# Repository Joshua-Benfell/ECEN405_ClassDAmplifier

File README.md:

# ECEN405_ClassDAmplifier

# Parts Checklist:
- [ ] [LPF 1](#lpf-1)
- [ ] [LPF 2](#lpf-2)
- [ ] [Gate Drivers](#gate-drivers) x 2
- [ ] Triangle wave generator block 
    - [ x ] [Comparator 1](#comparator-1) 
    - [ ] [Integrator](#integrator)
- [ ] [MOSFETs](#mosfets) x 2
- [ ] [Comparator 2](#comparator) 2
- [ ] [Inverter](#inverter)
- [ ] [Buffer](#buffer)

# System Overview
## Input Voltage
2V Peak to peak (+1V to -1V) with at least 1V input sensitivity. 

## Filters
### **Output Filter**
Needs to filter frequencies above 200Hz, but not the 200Hz point such that it has equivalent gain.  
Will likely need to be a Bridge Tied load (BTL) configuration, as BTL output filters do not require DC blocking caps, which limit the low frequency response of the amplifier, and can be quite large.  

Further reading: [on output filter types for class-d amplifiers](https://www.eetimes.com/understanding-output-filters-for-class-d-amplifiers/) and [BTL configurations on Wikipedia](https://en.wikipedia.org/wiki/Bridged_and_paralleled_amplifiers#Bridge-parallel_amplifier)  

### **Input Filter**
Cut-off point at 2kHz so that the cut-off is 1 decade above the 200Hz at the top of the bandwidth. This will avoid the phase change since it starts 1 decade before the cut-off. Make a Bode plot. No HPF for input as it is not needed. 
## Triangle Wave Generator
Possible approaches:
### **555 timer and an integrator**
To produce a clean triangle wave is complicated with a 555, simpler circuits with a 555 don't seem to guarantee a good output triangle wave. Furthermore, 55 timer circuits are more expensive and have a larger footprint.

### **Comparator integrator** 
A comparator integrator, is able to provide a reliably clean triangle wave and is fairly simple to implement.  
  
The frequency of the triangle wave will be above the audible range of frequencies at 22kHz.  
The package used will be: [MAX4016](https://www.digikey.co.nz/product-detail/en/maxim-integrated/MAX4016ESA/MAX4016ESA-ND/1702288)  
- 10V rail so that we don’t step down more again
- 5V middle because 50/50 v-divider is easy
- No dual rail because that is what a full bridge is for
- Also no whack shit - Danny B

## Switching Frequency
Two key constraints with switching frequency:  
1. As we are sampling an audio signal, it must be at least 10x the max frequency in our signal. The max signal frequency for the amplifier will be 200Hz, therefore the minimum sampling frequency must be 2kHz.
2. The switching frequency can't be audible, which means it must be outside of the audible range of frequencies to humans which is 20Hz - 20kHz. Adult humans typically can't hear more than 15 - 17kHz, making 20kHz a reasonable limit.
As a result the switching frequency must be **at least 20kHz**.

# Part Description and Justification
## LPF 1
## LPF 2
## Gate Drivers
### Requirements
- 18V Input
- 80W at 4 Ohms
- No integrated Fets
- Selectable Dead Time

### Selected
## Comparator 1
[MAX4016](https://www.digikey.co.nz/product-detail/en/maxim-integrated/MAX4016ESA/MAX4016ESA-ND/1702288)  
- 10V rail so that we don’t step down more again
- 5V middle because 50/50 v-divider is easy
- No dual rail because that is what a full bridge is for
- Also no whack shit - Danny B
## Integrator
## MOSFETs
## Comparator 2
## Inverter
## Buffer

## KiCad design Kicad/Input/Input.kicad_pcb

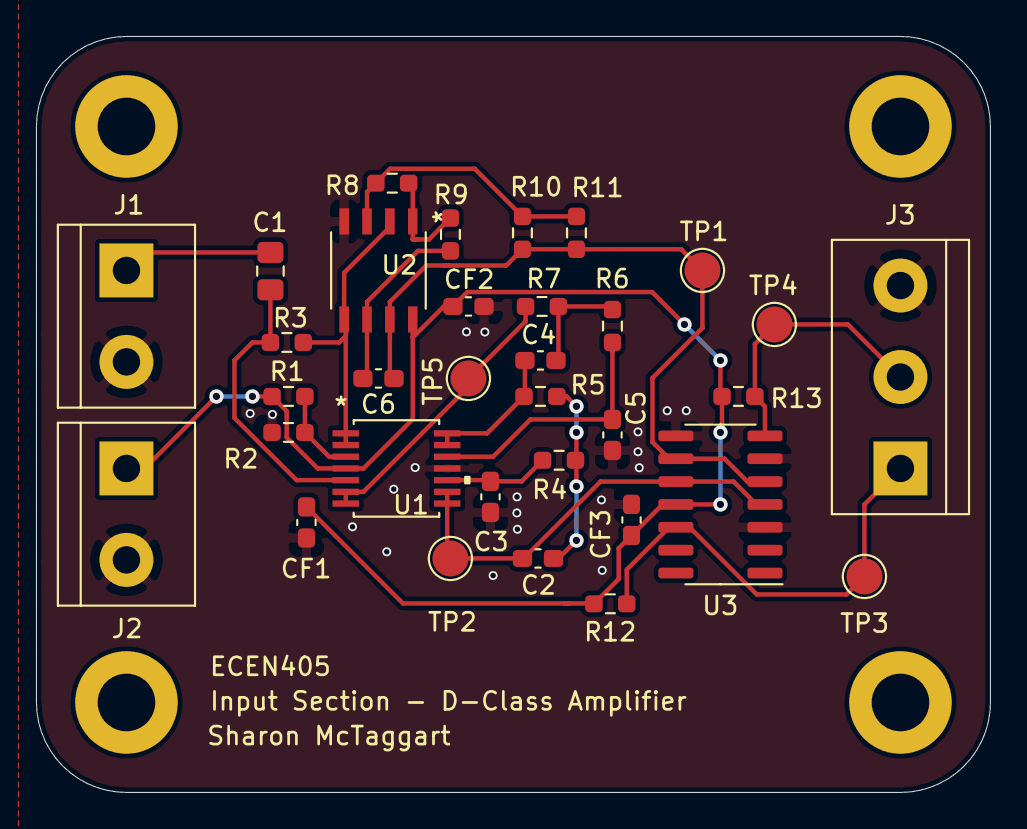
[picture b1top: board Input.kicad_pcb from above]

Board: 2 copper layers, 53.0 x 42.0 mm, 37 parts (0 on the bottom side), 19 nets.

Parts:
C1: 10u; C_0805_2012Metric_Pad1.18x1.45mm_HandSolder
C2: 56n; C_0603_1608Metric_Pad1.08x0.95mm_HandSolder
C3: 5.6n; C_0603_1608Metric_Pad1.08x0.95mm_HandSolder
C4: 47n; C_0603_1608Metric_Pad1.08x0.95mm_HandSolder
C5: 4.7n; C_0603_1608Metric_Pad1.08x0.95mm_HandSolder
C6: 10n; C_0603_1608Metric_Pad1.08x0.95mm_HandSolder
CF1, CF2, CF3: 100n; C_0603_1608Metric_Pad1.08x0.95mm_HandSolder
H1, H2, H3, H4: MountingHole; MountingHole_3.2mm_M3_ISO7380_Pad
J1, J2: Conn_01x02; TerminalBlock_bornier-2_P5.08mm
J3: Conn_01x03; TerminalBlock_bornier-3_P5.08mm
R1, R2, R4, R12, R13: 10k; R_0603_1608Metric_Pad0.98x0.95mm_HandSolder
R3: 16k; R_0603_1608Metric_Pad0.98x0.95mm_HandSolder
R5: 750; R_0603_1608Metric_Pad0.98x0.95mm_HandSolder
R6: 22k; R_0603_1608Metric_Pad0.98x0.95mm_HandSolder
R7: 620; R_0603_1608Metric_Pad0.98x0.95mm_HandSolder
R8: 27k; R_0603_1608Metric_Pad0.98x0.95mm_HandSolder
R9: 2.2k; R_0603_1608Metric_Pad0.98x0.95mm_HandSolder
R10, R11: 12k; R_0603_1608Metric_Pad0.98x0.95mm_HandSolder
TP1, TP2, TP3, TP4, TP5: TestPoint; TestPoint_Pad_D2.0mm
U1: AD8567ARUZ
U2: MAX4016ESA+; MAX4016ESA&plus_
U3: LM319; SO-14_3.9x8.65mm_P1.27mm

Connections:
/Comparator/INV_PWM_OUT: J3.2, R13.2, TP4.1, U3.7
/Comparator/PWM_OUT: J3.1, R12.2, TP3.1, U3.12
/Comparator/SIG_IN: C2.2, TP2.1, U1.8, U1.9, U3.4, U3.10
/Comparator/TRIANGLE_IN: C6.1, R10.2, R11.2, TP1.1, U2.7, U3.5, U3.9
/LPF/BIASED_SIG: R7.1, TP5.1, U1.6, U1.7
/LPF/Filter_FirstStage: C4.1, R5.1, U1.13, U1.14
/LPF/SIG_IN: C1.2, J1.1
/LPF/VREF: R3.1, U1.1, U1.2, U2.2, U2.5
GND: C3.2, C5.2, CF1.2, CF2.2, CF3.2, J1.2, J2.2, J3.3, R2.2, U1.11, U2.4, U3.3, U3.6, U3.8
unnamed: C1.1, R3.2, U1.5
unnamed: C2.1, R4.1, R5.2
unnamed: C3.1, R4.2, U1.10
unnamed: C4.2, R6.1, R7.2
unnamed: C5.1, R6.2, U1.12
unnamed: C6.2, R9.1, U2.6
unnamed: R1.2, R2.1, U1.3
unnamed: R8.1, R9.2, U2.1
unnamed: R8.2, R10.1, R11.1, U2.3
VCC: CF1.1, CF2.1, CF3.1, J2.1, R1.1, R12.1, R13.1, U1.4, U2.8, U3.11

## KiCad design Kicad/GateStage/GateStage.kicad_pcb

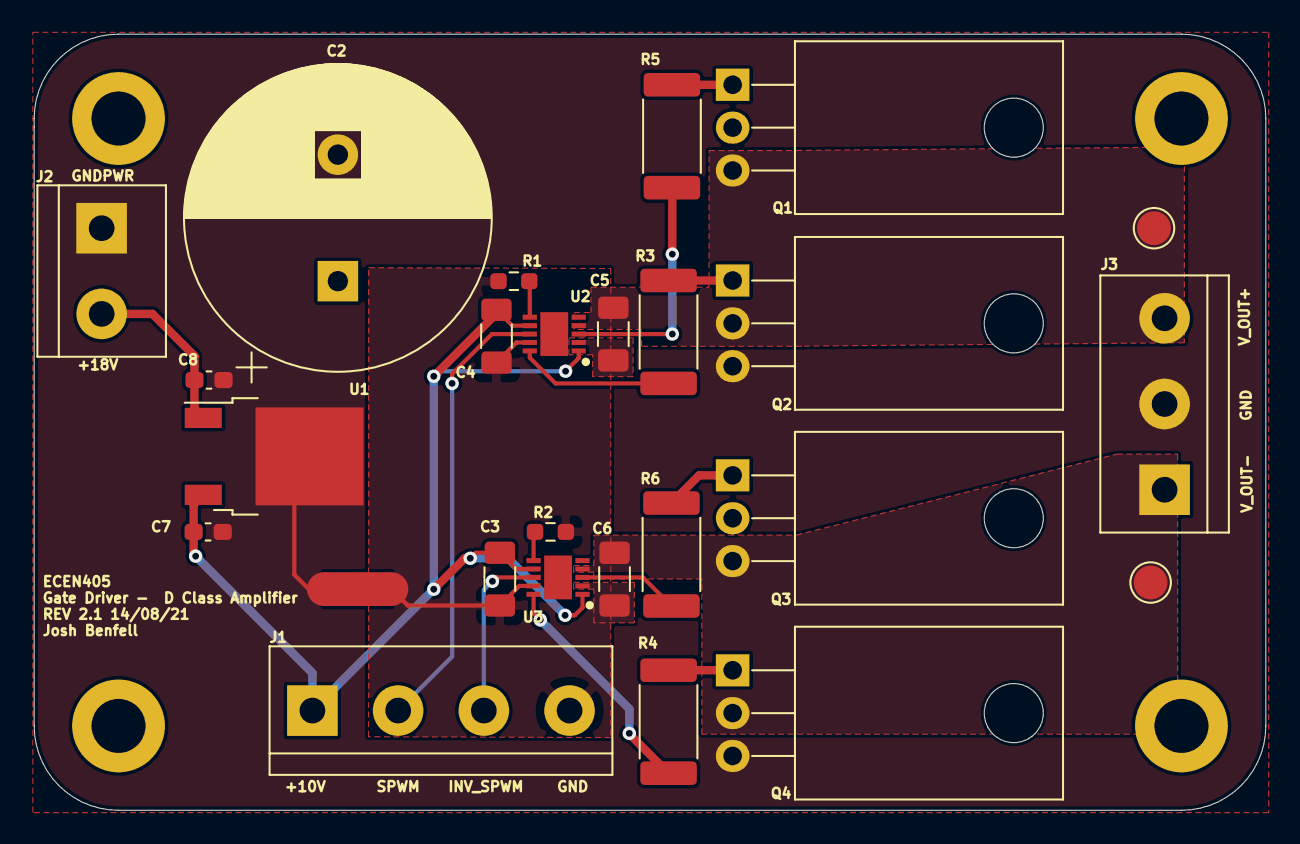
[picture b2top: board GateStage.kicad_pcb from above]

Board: 2 copper layers, 73.0 x 46.0 mm, 31 parts (1 on the bottom side), 20 nets.

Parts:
C1, C3, C4, C5, C6: 10u 50V; C_1206_3216Metric_Pad1.33x1.80mm_HandSolder
C2: 10m; CP_Radial_D18.0mm_P7.50mm
C7: 100n; C_0603_1608Metric_Pad1.08x0.95mm_HandSolder
C8: 330n; C_0603_1608Metric_Pad1.08x0.95mm_HandSolder
H1, H2, H3, H4: MountingHole; MountingHole_3.2mm_M3_ISO14580_Pad
J1: Conn_01x04; TerminalBlock_bornier-4_P5.08mm
J2: Conn_01x02; TerminalBlock_bornier-2_P5.08mm
J3: Conn_01x03; TerminalBlock_bornier-3_P5.08mm
NT1: Net-Tie_2; NetTie-2_SMD_Pad2.0mm
Q1, Q2, Q3, Q4: PHP23NQ11T,127; TO-220-3_Horizontal_TabDown
R1, R2: 20k; R_0603_1608Metric_Pad0.98x0.95mm_HandSolder
R3, R4, R5, R6: 10; R_2512_6332Metric_Pad1.40x3.35mm_HandSolder
TP1, TP2: TestPoint; TestPoint_Pad_D2.0mm
U1: L78M10ABDT; TO-252-2
U2, U3: DGD05463FN-7; SON50P300X300X80-11N-D

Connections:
/H-Bridge/V_DT1: R1.1, U2.6
/H-Bridge/V_DT2: R2.1, U3.6
/H-Bridge/V_OUT+: C5.1, J3.3, Q1.3, Q2.2, TP1.1, U2.4
/H-Bridge/V_OUT-: C6.1, J3.1, Q3.3, Q4.2, TP2.1, U3.4
/INV_PWM: J1.3, U3.8
/PWM: J1.2, U2.8
GND: C3.1, C4.1, J1.4, NT1.1, R1.2, R2.2, U2.9, U3.9
GNDPWR: C1.2, C2.2, C7.2, C8.2, J2.1, J3.2, NT1.2, Q2.3, Q4.3, U1.2
unnamed: C5.2, U2.2
unnamed: C6.2, U3.2
unnamed: Q1.1, R5.1
unnamed: Q2.1, R3.1
unnamed: Q3.1, R6.1
unnamed: Q4.1, R4.1
unnamed: R3.2, U2.10
unnamed: R4.2, U3.10
unnamed: R5.2, U2.3
unnamed: R6.2, U3.3
VCC: C3.2, C4.2, C7.1, J1.1, U1.3, U2.1, U2.7, U3.1, U3.7
VDD: C1.1, C2.1, C8.1, J2.2, Q1.2, Q3.2, U1.1

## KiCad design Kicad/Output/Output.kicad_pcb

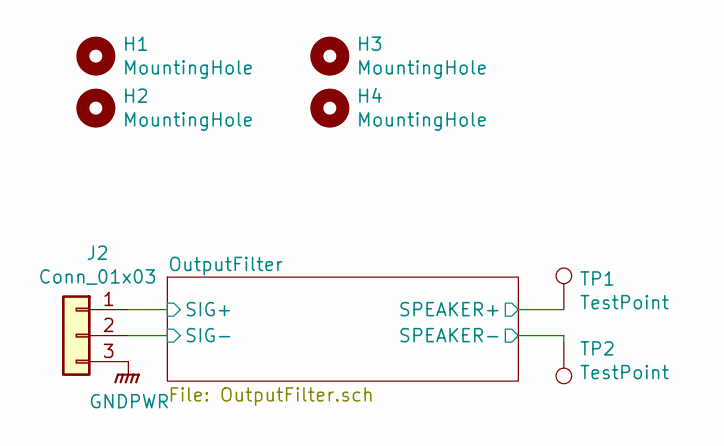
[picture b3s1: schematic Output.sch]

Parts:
H1, H2, H3, H4: MountingHole; MountingHole_3.2mm_M3_ISO7380_Pad
J2: Conn_01x03; TerminalBlock_bornier-3_P5.08mm
TP1, TP2: TestPoint; TestPoint_Pad_D2.0mm

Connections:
/OutputFilter/SIG+: J2.1; also elsewhere on the board
/OutputFilter/SIG-: J2.2; also elsewhere on the board
/OutputFilter/SPEAKER+: TP1.1; also elsewhere on the board
/OutputFilter/SPEAKER-: TP2.1; also elsewhere on the board
GNDPWR: J2.3; also elsewhere on the board

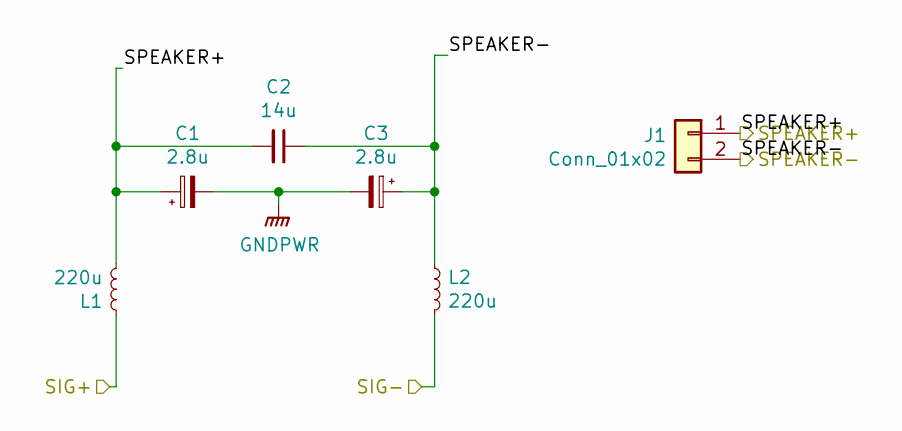
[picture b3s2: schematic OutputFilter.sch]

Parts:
C1, C3: 2.8u; CP_Radial_D8.0mm_P3.50mm
C2: 14u; C4AQLBU5140M18K
J1: Conn_01x02; TerminalBlock_bornier-2_P5.08mm
L1, L2: 220u; IND_HCTI-220-5.8

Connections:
/OutputFilter/SIG+: L1.1; also elsewhere on the board
/OutputFilter/SIG-: L2.2; also elsewhere on the board
/OutputFilter/SPEAKER+: C1.1, C2.2, J1.1, L1.2; also elsewhere on the board
/OutputFilter/SPEAKER-: C2.1, C3.1, J1.2, L2.1; also elsewhere on the board
GNDPWR: C1.2, C3.2; also elsewhere on the board

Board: 2 copper layers, 13 parts (0 on the bottom side), 5 nets, no tracks yet.

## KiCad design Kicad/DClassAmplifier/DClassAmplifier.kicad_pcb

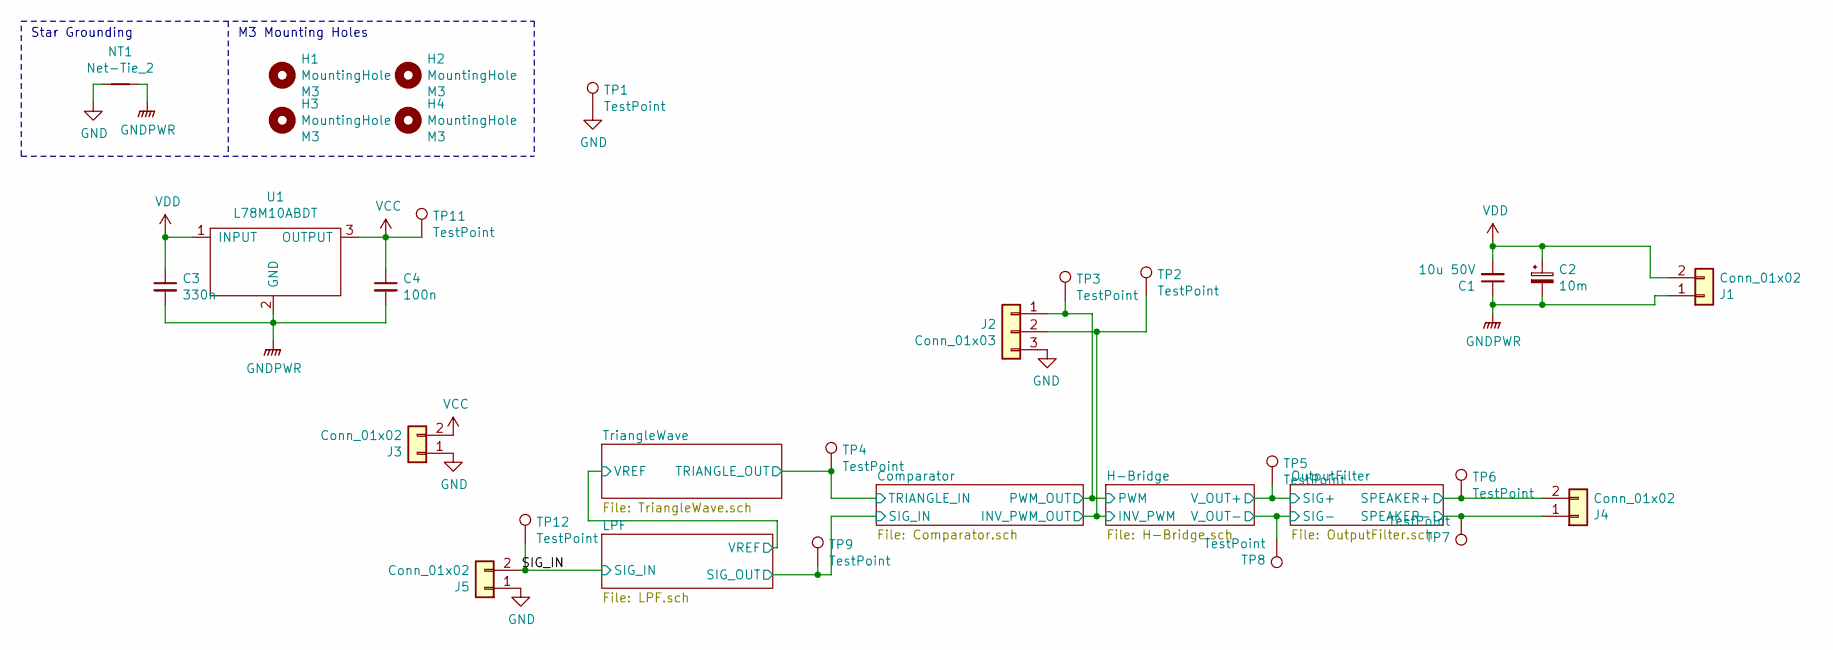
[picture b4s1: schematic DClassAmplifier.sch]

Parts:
C1: 10u 50V; C_1206_3216Metric_Pad1.33x1.80mm_HandSolder
C2: 10m; CP_Radial_D18.0mm_P7.50mm
C3: 330n; C_0603_1608Metric_Pad1.08x0.95mm_HandSolder
C4: 100n; C_0603_1608Metric_Pad1.08x0.95mm_HandSolder
H1, H2, H3, H4: MountingHole; MountingHole_3.2mm_M3_ISO7380_Pad
J1, J3, J4, J5: Conn_01x02; TerminalBlock_bornier-2_P5.08mm
J2: Conn_01x03; TerminalBlock_bornier-3_P5.08mm
NT1: Net-Tie_2; NetTie-2_SMD_Pad2.0mm
TP1, TP2, TP3, TP4, TP5, TP6, TP7, TP8, TP9, TP11, TP12: TestPoint; TestPoint_THTPad_D1.5mm_Drill0.7mm
U1: L78M10ABDT; TO-252-2

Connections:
/Comparator/SIG_IN: TP9.1; also elsewhere on the board
/Comparator/TRIANGLE_IN: TP4.1; also elsewhere on the board
/H-Bridge/INV_PWM: J2.2, TP2.1; also elsewhere on the board
/H-Bridge/PWM: J2.1, TP3.1; also elsewhere on the board
/OutputFilter/SIG+: TP5.1; also elsewhere on the board
/OutputFilter/SIG-: TP8.1; also elsewhere on the board
/OutputFilter/SPEAKER+: J4.2, TP6.1; also elsewhere on the board
/OutputFilter/SPEAKER-: J4.1, TP7.1; also elsewhere on the board
/SIG_IN: J5.2, TP12.1; also elsewhere on the board
GND: J2.3, J3.1, J5.1, NT1.1, TP1.1; also elsewhere on the board
GNDPWR: C1.1, C2.2, C3.2, C4.2, J1.1, NT1.2, U1.2 (GND); also elsewhere on the board
VCC: C4.1, J3.2, TP11.1, U1.3 (OUTPUT); also elsewhere on the board
VDD: C1.2, C2.1, C3.1, J1.2, U1.1 (INPUT); also elsewhere on the board

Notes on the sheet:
Star Grounding
M3 Mounting Holes

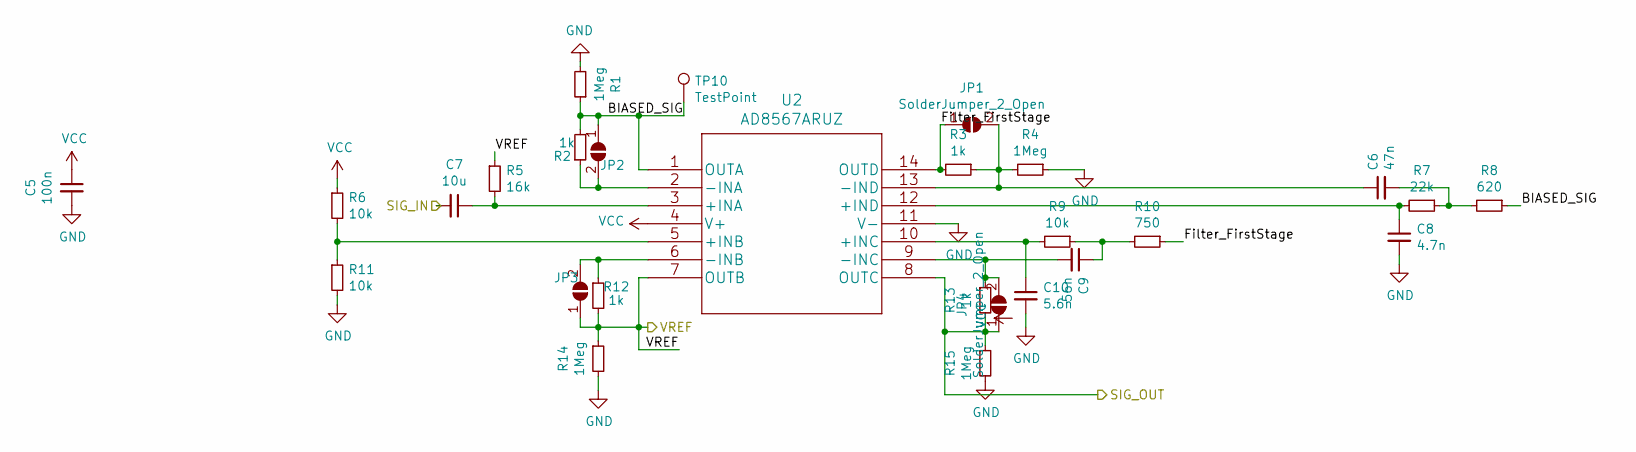
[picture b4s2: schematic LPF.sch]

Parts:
C5: 100n; C_0603_1608Metric_Pad1.08x0.95mm_HandSolder
C6: 47n; C_0603_1608Metric_Pad1.08x0.95mm_HandSolder
C7: 10u; C_0603_1608Metric_Pad1.08x0.95mm_HandSolder
C8: 4.7n; C_0603_1608Metric_Pad1.08x0.95mm_HandSolder
C9: 56n; C_0603_1608Metric_Pad1.08x0.95mm_HandSolder
C10: 5.6n; C_0603_1608Metric_Pad1.08x0.95mm_HandSolder
JP1, JP2, JP3, JP4: SolderJumper_2_Open; SolderJumper-2_P1.3mm_Open_RoundedPad1.0x1.5mm
R1, R4, R14, R15: 1Meg; R_0603_1608Metric_Pad0.98x0.95mm_HandSolder
R2, R3, R12, R13: 1k; R_0603_1608Metric_Pad0.98x0.95mm_HandSolder
R5: 16k; R_0603_1608Metric_Pad0.98x0.95mm_HandSolder
R6, R9, R11: 10k; R_0603_1608Metric_Pad0.98x0.95mm_HandSolder
R7: 22k; R_0603_1608Metric_Pad0.98x0.95mm_HandSolder
R8: 620; R_0603_1608Metric_Pad0.98x0.95mm_HandSolder
R10: 750; R_0603_1608Metric_Pad0.98x0.95mm_HandSolder
TP10: TestPoint; TestPoint_THTPad_D1.5mm_Drill0.7mm
U2: AD8567ARUZ

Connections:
/Comparator/SIG_IN: JP4.1 (A), R13.2, R15.1, U2.8 (OUTC); also elsewhere on the board
/LPF/BIASED_SIG: JP2.1 (A), R1.1, R2.2, R8.1, TP10.1, U2.1 (OUTA)
/LPF/Filter_FirstStage: JP1.1 (A), R3.2, R10.1, U2.14 (OUTD)
/LPF/VREF: JP3.1 (A), R5.1, R12.2, R14.1, U2.7 (OUTB); also elsewhere on the board
/SIG_IN: C7.2; also elsewhere on the board
GND: C5.2, C8.2, C10.2, R1.2, R4.1, R11.2, R14.2, R15.2, U2.11 (V-); also elsewhere on the board
unnamed: C6.1, JP1.2 (B), R3.1, R4.2, U2.13 (-IND)
unnamed: C6.2, R7.1, R8.2
unnamed: C7.1, R5.2, U2.3 (+INA)
unnamed: C8.1, R7.2, U2.12 (+IND)
unnamed: C9.1, R9.1, R10.2
unnamed: C9.2, JP4.2 (B), R13.1, U2.9 (-INC)
unnamed: C10.1, R9.2, U2.10 (+INC)
unnamed: JP2.2 (B), R2.1, U2.2 (-INA)
unnamed: JP3.2 (B), R12.1, U2.6 (-INB)
unnamed: R6.2, R11.1, U2.5 (+INB)
VCC: C5.1, R6.1, U2.4 (V+); also elsewhere on the board

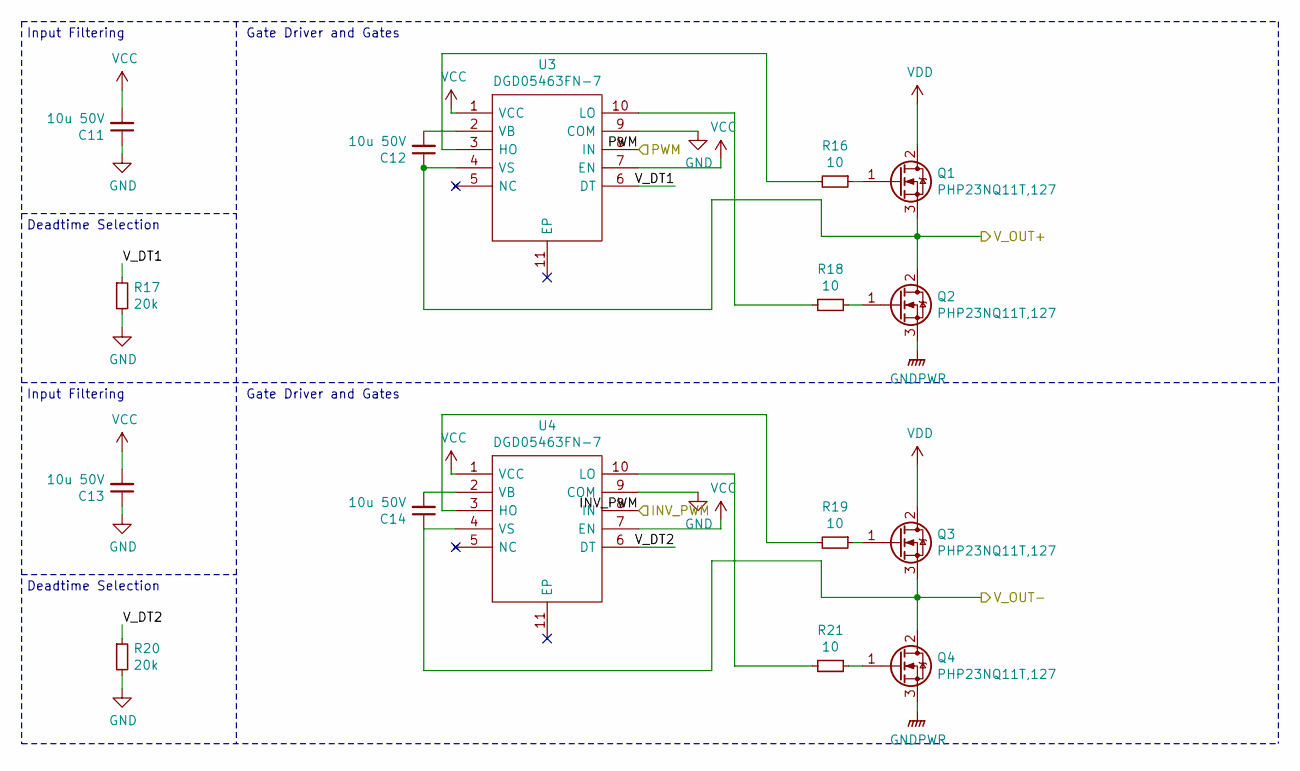
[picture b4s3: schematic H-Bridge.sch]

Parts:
C11, C12, C13, C14: 10u 50V; C_1206_3216Metric_Pad1.33x1.80mm_HandSolder
Q1, Q2, Q3, Q4: PHP23NQ11T,127; TO-220-3_Horizontal_TabDown
R16, R18, R19, R21: 10; R_2512_6332Metric_Pad1.40x3.35mm_HandSolder
R17, R20: 20k; R_0603_1608Metric_Pad0.98x0.95mm_HandSolder
U3, U4: DGD05463FN-7; SON50P300X300X80-11N-D; Manufacturer_Part_Number DGD05463FN-7; Mouser Part Number 621-DGD05463FN-7

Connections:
/H-Bridge/INV_PWM: U4.8 (IN); also elsewhere on the board
/H-Bridge/PWM: U3.8 (IN); also elsewhere on the board
/H-Bridge/V_DT1: R17.1, U3.6 (DT)
/H-Bridge/V_DT2: R20.1, U4.6 (DT)
/OutputFilter/SIG+: C12.1, Q1.3 (S), Q2.2 (D), U3.4 (VS); also elsewhere on the board
/OutputFilter/SIG-: C14.1, Q3.3 (S), Q4.2 (D), U4.4 (VS); also elsewhere on the board
GND: C11.1, C13.1, R17.2, R20.2, U3.9 (COM), U4.9 (COM); also elsewhere on the board
GNDPWR: Q2.3 (S), Q4.3 (S); also elsewhere on the board
unnamed: C12.2, U3.2 (VB)
unnamed: C14.2, U4.2 (VB)
unnamed: Q1.1 (G), R16.1
unnamed: Q2.1 (G), R18.1
unnamed: Q3.1 (G), R19.1
unnamed: Q4.1 (G), R21.1
unnamed: R16.2, U3.3 (HO)
unnamed: R18.2, U3.10 (LO)
unnamed: R19.2, U4.3 (HO)
unnamed: R21.2, U4.10 (LO)
VCC: C11.2, C13.2, U3.1 (VCC), U3.7 (EN), U4.1 (VCC), U4.7 (EN); also elsewhere on the board
VDD: Q1.2 (D), Q3.2 (D); also elsewhere on the board

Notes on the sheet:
Input Filtering
Deadtime Selection
Gate Driver and Gates

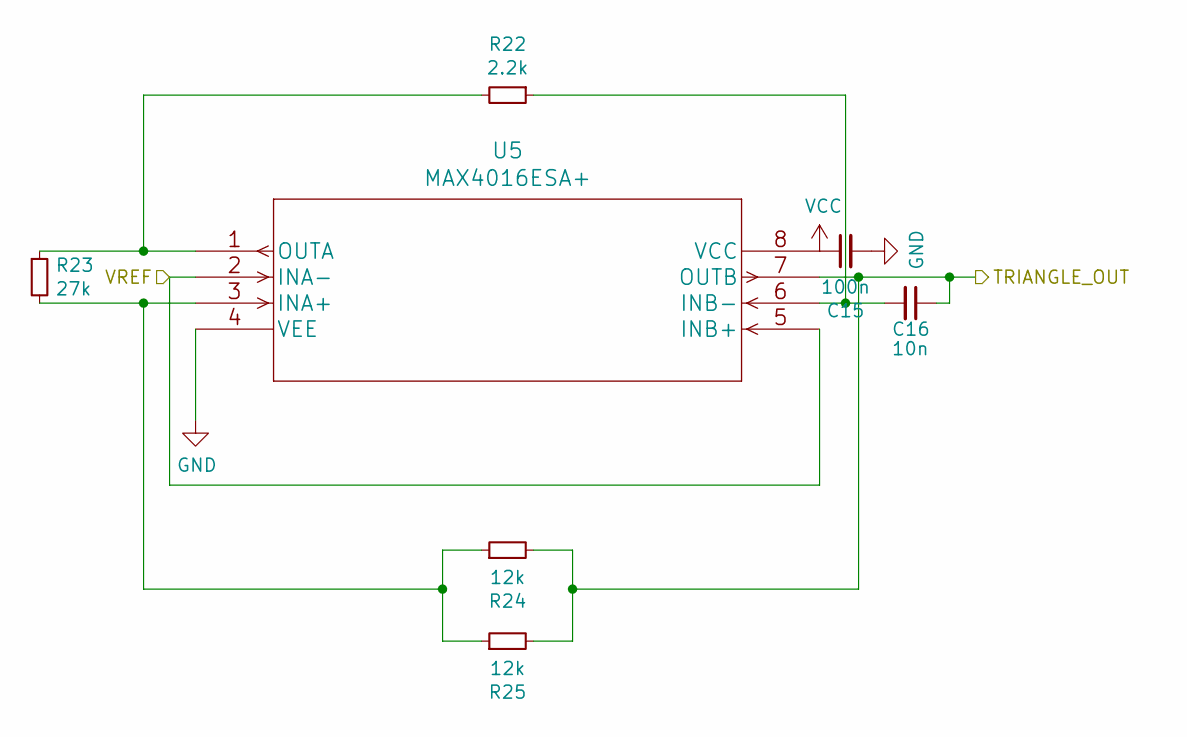
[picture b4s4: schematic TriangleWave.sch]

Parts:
C15: 100n; C_0603_1608Metric_Pad1.08x0.95mm_HandSolder
C16: 10n; C_0603_1608Metric_Pad1.08x0.95mm_HandSolder
R22: 2.2k; R_0603_1608Metric_Pad0.98x0.95mm_HandSolder
R23: 27k; R_0603_1608Metric_Pad0.98x0.95mm_HandSolder
R24, R25: 12k; R_0603_1608Metric_Pad0.98x0.95mm_HandSolder
U5: MAX4016ESA+; MAX4016ESA&plus_

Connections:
/Comparator/TRIANGLE_IN: C16.1, R24.2, R25.2, U5.7 (OUTB); also elsewhere on the board
/LPF/VREF: U5.2 (INA-), U5.5 (INB+); also elsewhere on the board
GND: C15.2, U5.4 (VEE); also elsewhere on the board
unnamed: C16.2, R22.1, U5.6 (INB-)
unnamed: R22.2, R23.1, U5.1 (OUTA)
unnamed: R23.2, R24.1, R25.1, U5.3 (INA+)
VCC: C15.1, U5.8 (VCC); also elsewhere on the board

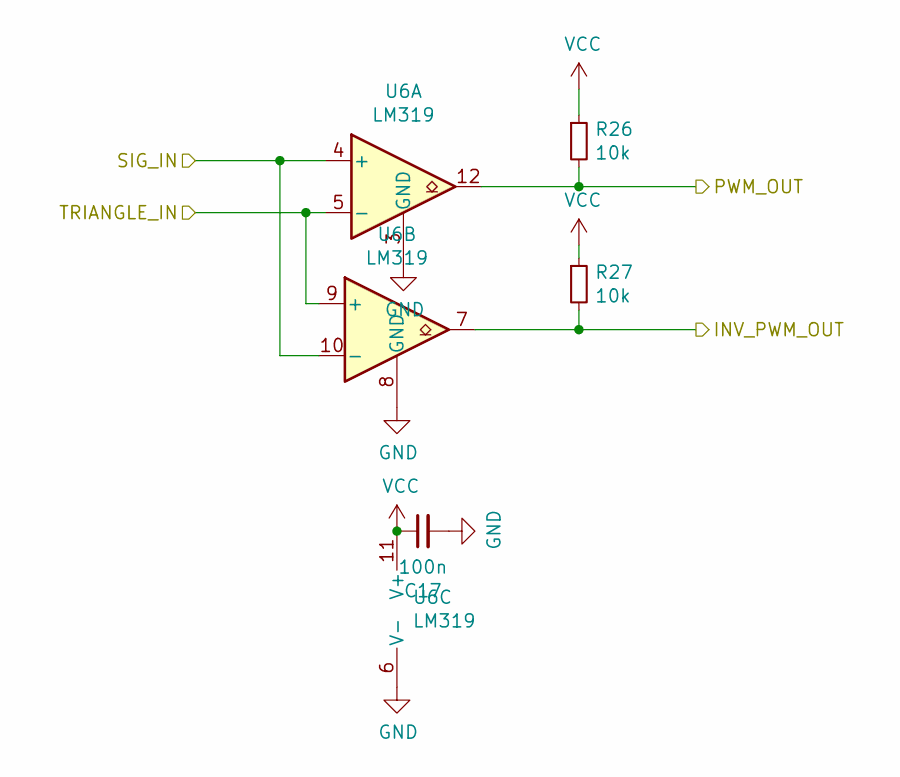
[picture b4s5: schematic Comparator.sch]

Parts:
C17: 100n; C_0603_1608Metric_Pad1.08x0.95mm_HandSolder
R26, R27: 10k; R_0603_1608Metric_Pad0.98x0.95mm_HandSolder
U6: LM319; SO-14_3.9x8.65mm_P1.27mm

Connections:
/Comparator/SIG_IN: U6.4 (+), U6.10 (-); also elsewhere on the board
/Comparator/TRIANGLE_IN: U6.5 (-), U6.9 (+); also elsewhere on the board
/H-Bridge/INV_PWM: R27.2, U6.7; also elsewhere on the board
/H-Bridge/PWM: R26.2, U6.12; also elsewhere on the board
GND: C17.2, U6.3 (GND), U6.6 (V-), U6.8 (GND); also elsewhere on the board
VCC: C17.1, R26.1, R27.1, U6.11 (V+); also elsewhere on the board

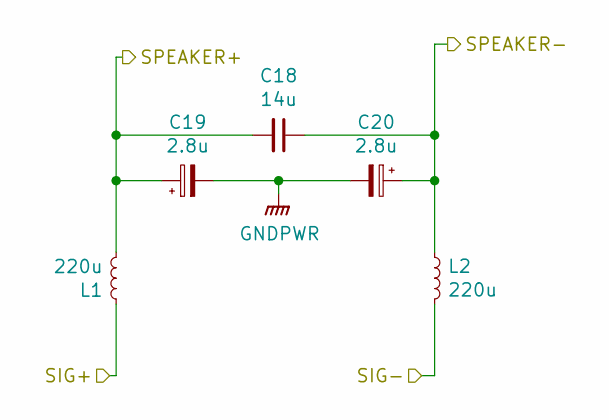
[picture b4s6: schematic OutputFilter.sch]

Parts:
C18: 14u; C4AQLBU5140M18K
C19, C20: 2.8u; CP_Radial_D8.0mm_P3.50mm
L1, L2: 220u; IND_HCTI-220-5.8

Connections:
/OutputFilter/SIG+: L1.1; also elsewhere on the board
/OutputFilter/SIG-: L2.2; also elsewhere on the board
/OutputFilter/SPEAKER+: C18.2, C19.1, L1.2; also elsewhere on the board
/OutputFilter/SPEAKER-: C18.1, C20.1, L2.1; also elsewhere on the board
GNDPWR: C19.2, C20.2; also elsewhere on the board

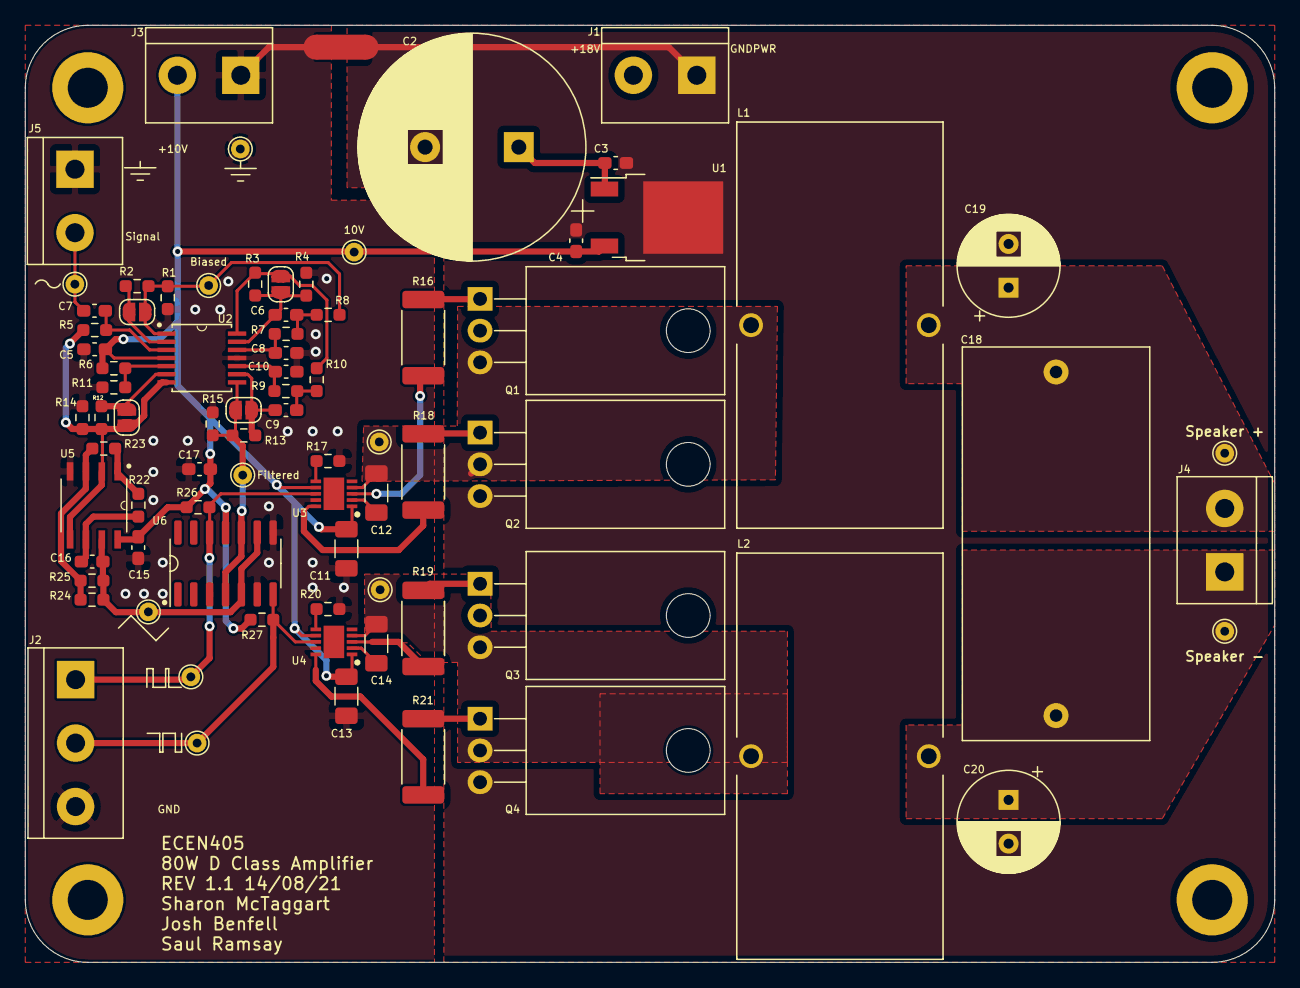
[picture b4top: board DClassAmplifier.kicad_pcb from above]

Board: 2 copper layers, 100.0 x 75.0 mm, 85 parts (1 on the bottom side), 41 nets.

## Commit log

2021-07-21 Initial Kicad File Commit
2021-07-25 Added Net-Tied Grounds and Filter schematic
2021-07-25 Create Additional Needed Hierarchical Schematics. Add Mounting Holes
2021-07-25 Add Gate Driver Library and To Schematic
2021-07-26 Project readme create and fill headers
2021-07-27 Made the list a checklist
2021-07-27 FET Selection
2021-07-27 Create triangleWaveGen
2021-07-28 Update Triangle Wave
2021-07-29 Sizing Gate Driver Components
2021-07-30 Start Output Filter Spice File
2021-07-30 Work on getting filters working
2021-07-30 Added Dummy Comparator to schematic and duplicated drive.
2021-08-03 Hierarchical Comparator Sheet
    Updated Gate Driver as well
2021-08-03 Input stage
2021-08-03 Add files via upload
    Summing circuit with dual 10V rails to add a 5V bias
2021-08-03 Spice Updates?
2021-08-03 10V input triangle wave
2021-08-03 Combine Triangle wave and Input Biasing/Filtering
2021-08-03 Lol Whoops, changes??
    Oh it was me moving things around a little bit
2021-08-04 transferred most info from google doc to readme
2021-08-04 Design Updates for LTSpice and KiCad
2021-08-07 Design from 6-8-21
2021-08-07 Values fixed
    40kHz triangle wave. Active LPF with 2kHz cut-off frequency.
2021-08-07 Seems fine
2021-08-07 Update gitignore to ignore LTSpice files
2021-08-07 Update Output Filter
2021-08-07 Gate Driver Footprint
2021-08-08 Output & Input Filter Final Designs
2021-08-08 Add Component Libraries
2021-08-08 Finish off Main Part of Schematic
2021-08-08 updates to schematic
2021-08-08 Add Filter Op Amp
2021-08-08 Update Opamp for Input Filter
2021-08-08 Added footprints to schematic
2021-08-08 Update Terminal Block Footprints
2021-08-08 Add Test Points
2021-08-08 Load Components into PCBDOC
2021-08-08 Add 3D Models
2021-08-09 Remove Spice Log Files
2021-08-09 Add 10m Resevoir Cap
2021-08-10 Added input to global schematic
    Changed the sig_in net label in the LPF sheet to a hierarchical net label of the same name
2021-08-10 Create Separate Projects for Each Board Layout
2021-08-11 Prepared O/P Filter PCB for track layout
    Laid out components for Output Filter PCB compactly ready for tracks to be drawn. Have drawn out precise margin lines too.
2021-08-11 Gate Drive Board V 1
2021-08-11 Updated Output Filter
2021-08-11 Saving changes before updating library
2021-08-11 OP Filter PCB Done
    OP Filter PCB finished
2021-08-11 Input PCB added
2021-08-12 SilkS on Gate Driver Board
2021-08-12 Flipped J2, added connector labels
    Flipped J2 and re-drew planes to connect Sig + and - respectively .
    Also added labels for all the connections for J1 and J2 as well as the testpoints
2021-08-12 PCB for input and added filter caps
2021-08-12 Switched around component sides to match connector
2021-08-12 Moved filter caps (slightly)
    Shifted them such that they're as close as possible to the larger cap with enough physical clearance, and made the both symmetrical too
2021-08-12 Add SilkScreen to Film Cap Footprint
2021-08-12 Add Alternative Cap Footprint
2021-08-12 Add Alternative Cap 3D Model
2021-08-12 Combined Board
2021-08-14 Add 10V Reg and Reroute
2021-08-14 Graphics and SilkScreen Improvement
2021-08-14 Generate Fabrication Outputs
2021-08-14 Whoops final Save
2021-08-14 Redo GateStage Board
2021-08-14 Move Combined Board Fabrication Outputs
2021-08-14 Create GateStage Fabrication Outputs
2021-08-15 Make Output Filter Board Smaller
2021-08-15 Label GateStage Board, Redo Planes, Regen Fab Outs
2021-08-15 resized input board
2021-08-15 added gerber and drill files
2021-08-16 Final Fab Files
2021-10-26 Image Dump
2021-11-02 Figure update

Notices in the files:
parts and their libraries:
Copyright 2021 Accelerated Designs. All rights reserved.
